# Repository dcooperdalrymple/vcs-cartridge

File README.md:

# Atari 2600/VCS EEPROM Cartridge

Simple 2k/4k Atari 2600 cartridge using easily writable EEPROM DIP chips as large as 32 kilobytes with manual bank selection using solder jumpers to store as many as 8 cartridge images. Requires a 74LS04 hex inverter to handle the chip enable signal to the ROM.

| Top                                                | Bottom                                                      |
| -------------------------------------------------- | ----------------------------------------------------------- |
|  |  |

Created using KiCad 7 under the GPL v3.0 license. Based on [Pixels Past cartridge](https://grandideastudio.com/portfolio/gaming/pixels-past/) originally manufactured and distributed by [AtariAge](https://www.atariage.com/).

## Compatible EEPROMs

* AT28C256
* AT28C64
* AT28C32
* AT28C16

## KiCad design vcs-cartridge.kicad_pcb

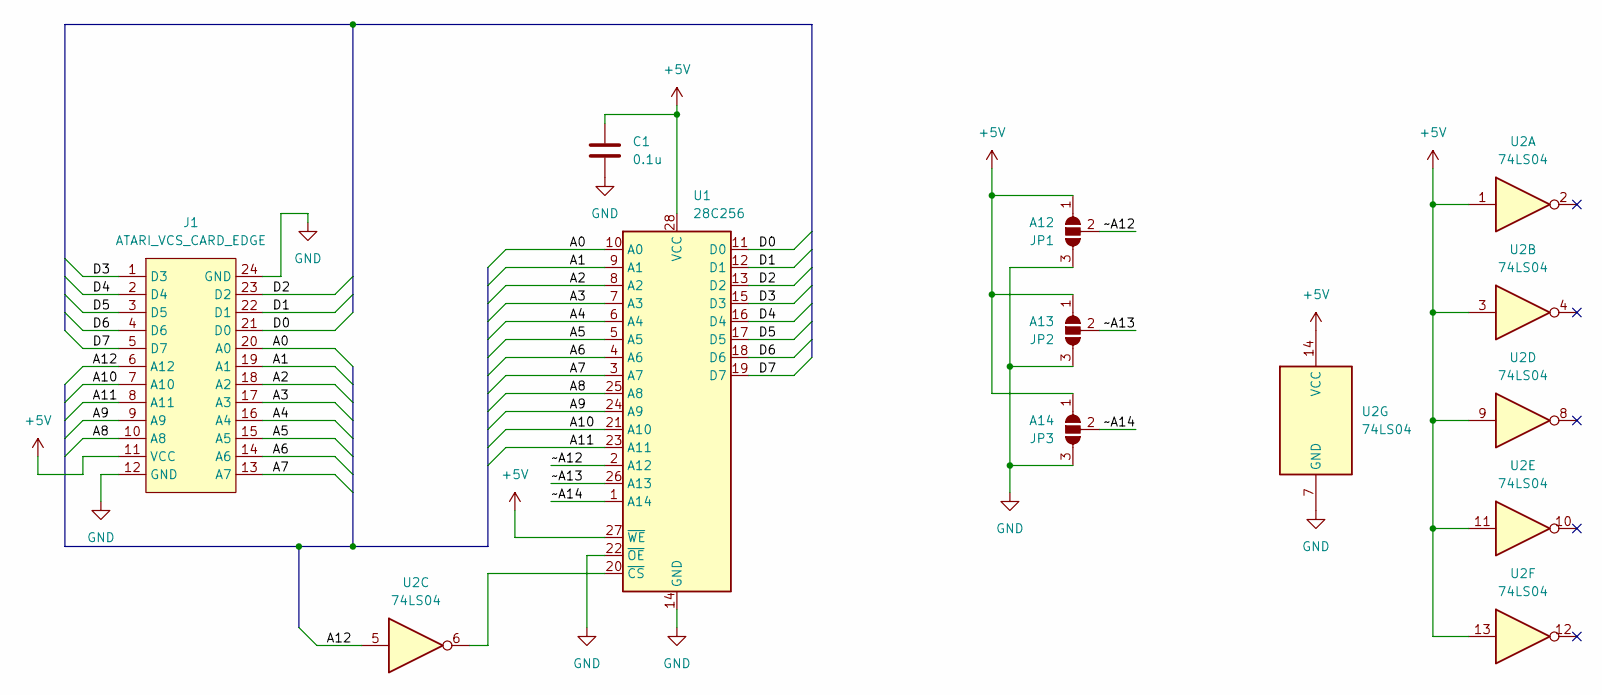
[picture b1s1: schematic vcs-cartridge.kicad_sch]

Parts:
C1: 0.1u; C_Rect_L4.6mm_W2.0mm_P2.50mm_MKS02_FKP02
J1: ATARI_VCS_CARD_EDGE
JP1: A12; SolderJumper-3_P1.3mm_Open_RoundedPad1.0x1.5mm
JP2: A13; SolderJumper-3_P1.3mm_Open_RoundedPad1.0x1.5mm
JP3: A14; SolderJumper-3_P1.3mm_Open_RoundedPad1.0x1.5mm
U1: 28C256; DIP-28_W15.24mm_LongPads
U2: 74LS04; DIP-14_W7.62mm_LongPads

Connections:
+5V: C1.1, J1.11 (VCC), JP1.1 (A), JP2.1 (A), JP3.1 (A), U1.27 (~WE), U1.28 (VCC), U2.1, U2.3, U2.9, U2.11, U2.13, U2.14 (VCC)
/A0: J1.20 (A0), U1.10 (A0)
/A1: J1.19 (A1), U1.9 (A1)
/A2: J1.18 (A2), U1.8 (A2)
/A3: J1.17 (A3), U1.7 (A3)
/A4: J1.16 (A4), U1.6 (A4)
/A5: J1.15 (A5), U1.5 (A5)
/A6: J1.14 (A6), U1.4 (A6)
/A7: J1.13 (A7), U1.3 (A7)
/A8: J1.10 (A8), U1.25 (A8)
/A9: J1.9 (A9), U1.24 (A9)
/A10: J1.7 (A10), U1.21 (A10)
/A11: J1.8 (A11), U1.23 (A11)
/A12: J1.6 (A12), U2.5
/D0: J1.21 (D0), U1.11 (D0)
/D1: J1.22 (D1), U1.12 (D1)
/D2: J1.23 (D2), U1.13 (D2)
/D3: J1.1 (D3), U1.15 (D3)
/D4: J1.2 (D4), U1.16 (D4)
/D5: J1.3 (D5), U1.17 (D5)
/D6: J1.4 (D6), U1.18 (D6)
/D7: J1.5 (D7), U1.19 (D7)
/~A12: JP1.2 (C), U1.2 (A12)
/~A13: JP2.2 (C), U1.26 (A13)
/~A14: JP3.2 (C), U1.1 (A14)
GND: C1.2, J1.12 (GND), J1.24 (GND), JP1.3 (B), JP2.3 (B), JP3.3 (B), U1.14 (GND), U1.22 (~OE), U2.7 (GND)
unnamed: U1.20 (~CS), U2.6

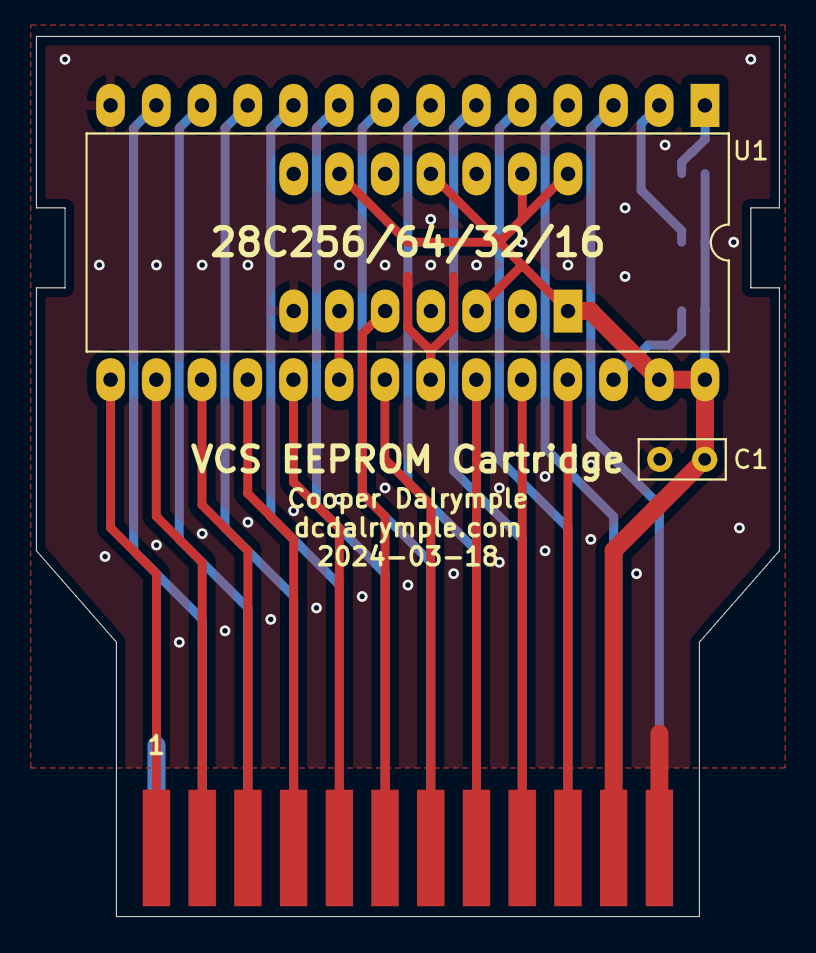
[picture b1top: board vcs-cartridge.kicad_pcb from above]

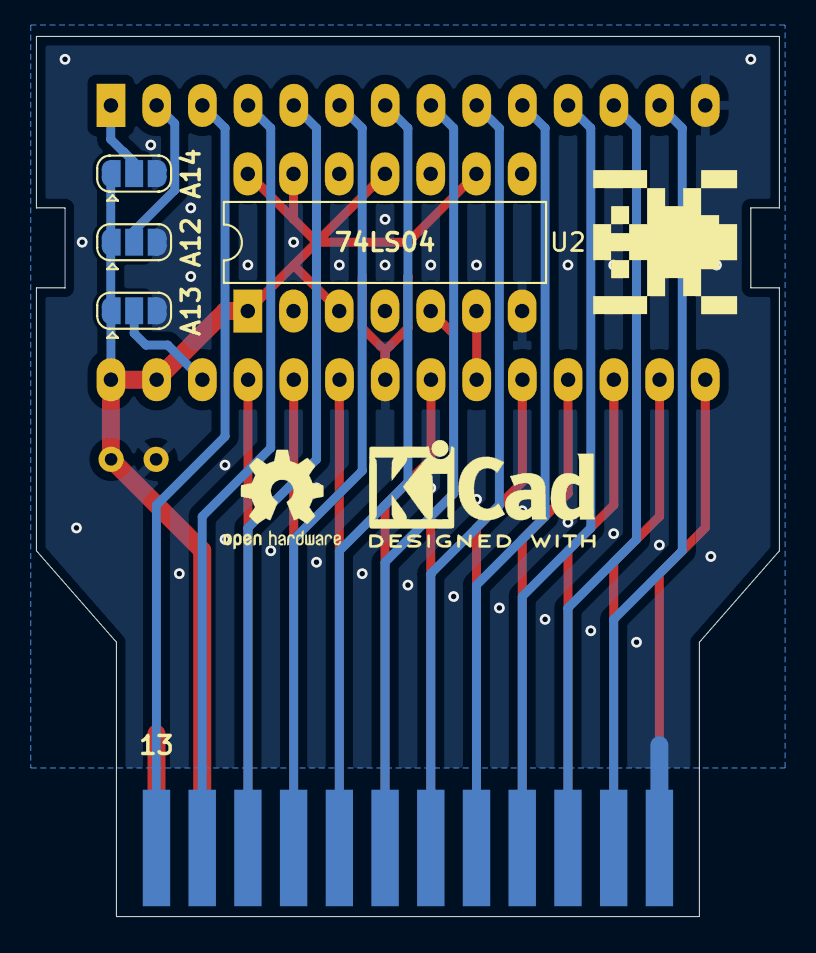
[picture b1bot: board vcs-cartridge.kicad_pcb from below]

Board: 2 copper layers, 41.3 x 48.9 mm, 7 parts (4 on the bottom side), 27 nets.

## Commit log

2024-03-18 First hardware design.
2024-03-18 Added readme and schematic pdf.
2024-03-18 Added reference to KiCad within readme.
2024-03-18 Added 3d render images.
